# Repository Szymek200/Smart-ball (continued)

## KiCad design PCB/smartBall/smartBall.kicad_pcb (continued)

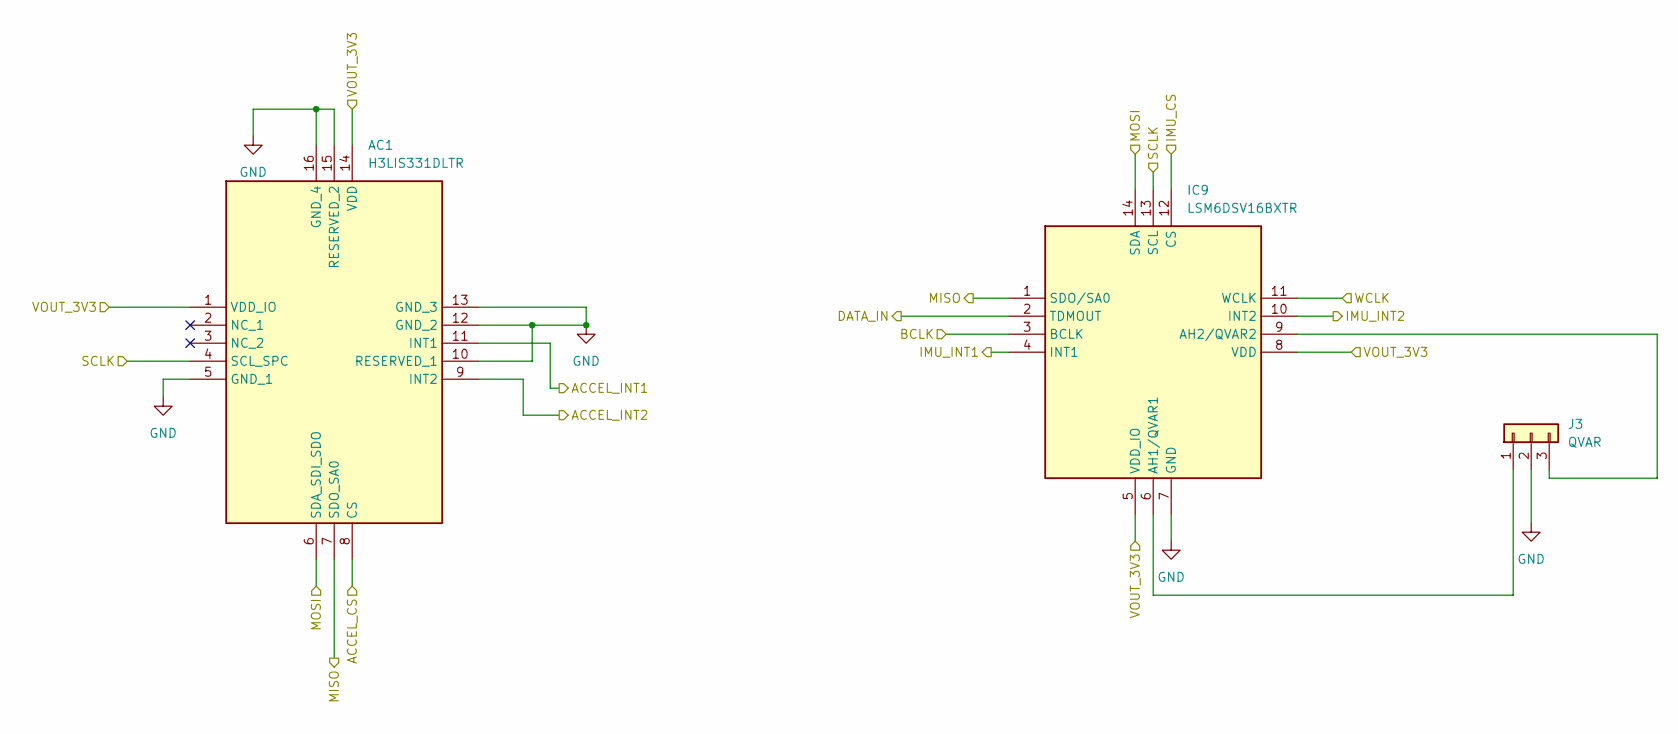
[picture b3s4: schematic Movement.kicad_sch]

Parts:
AC1: H3LIS331DLTR; LIS3DHTR; Mouser Part Number 511-H3LIS331DLTR
IC9: LSM6DSV16BXTR; Mouser Part Number 511-LSM6DSV16BXTR
J3: QVAR; JST_PH_B3B-PH-K_1x03_P2.00mm_Vertical

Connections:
/Power/Movement/ACCEL_CS: AC1.8 (CS); also elsewhere on the board
/Power/Movement/ACCEL_INT1: AC1.11 (INT1); also elsewhere on the board
/Power/Movement/ACCEL_INT2: AC1.9 (INT2); also elsewhere on the board
/Power/Movement/BCLK: IC9.3 (BCLK); also elsewhere on the board
/Power/Movement/DATA_IN: IC9.2 (TDMOUT); also elsewhere on the board
/Power/Movement/IMU_CS: IC9.12 (CS); also elsewhere on the board
/Power/Movement/IMU_INT1: IC9.4 (INT1); also elsewhere on the board
/Power/Movement/IMU_INT2: IC9.10 (INT2); also elsewhere on the board
/Power/Movement/MISO: AC1.7 (SDO_SA0), IC9.1 (SDO/SA0); also elsewhere on the board
/Power/Movement/MOSI: AC1.6 (SDA_SDI_SDO), IC9.14 (SDA); also elsewhere on the board
/Power/Movement/SCLK: AC1.4 (SCL_SPC), IC9.13 (SCL); also elsewhere on the board
/Power/Movement/VOUT_3V3: AC1.1 (VDD_IO), AC1.14 (VDD), IC9.5 (VDD_IO), IC9.8 (VDD); also elsewhere on the board
/Power/Movement/WCLK: IC9.11 (WCLK); also elsewhere on the board
GND: AC1.5 (GND_1), AC1.10 (RESERVED_1), AC1.12 (GND_2), AC1.13 (GND_3), AC1.15 (RESERVED_2), AC1.16 (GND_4), IC9.7 (GND), J3.2; also elsewhere on the board
unnamed: IC9.6 (AH1/QVAR1), J3.1
unnamed: IC9.9 (AH2/QVAR2), J3.3

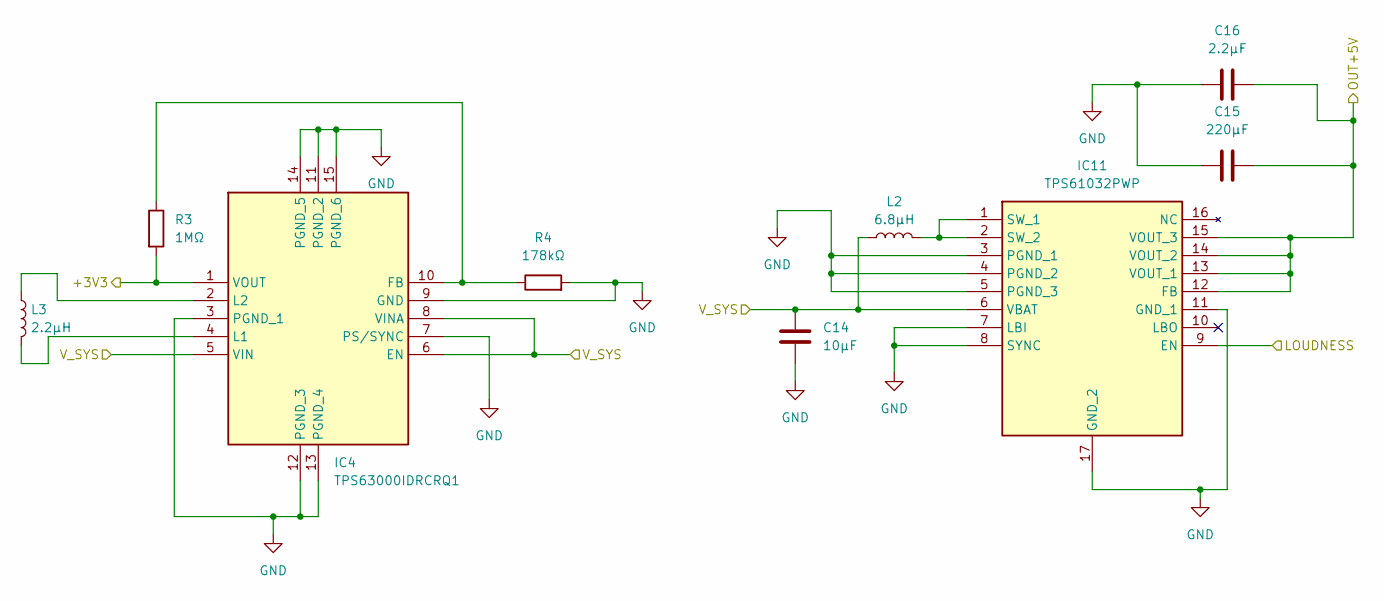
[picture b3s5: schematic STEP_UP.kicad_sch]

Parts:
C14: 10µF; C_Disc_D5.0mm_W2.5mm_P2.50mm
C15: 220µF; C_Disc_D5.0mm_W2.5mm_P2.50mm
C16: 2.2µF; C_Disc_D5.0mm_W2.5mm_P2.50mm
IC4: TPS63000IDRCRQ1; Mouser Part Number 595-TPS63000IDRCRQ1
IC11: TPS61032PWP; SOP65P640X120-17N; Mouser Part Number 595-TPS61032PWP
L2: 6.8µH; L_Axial_L7.0mm_D3.3mm_P10.16mm_Horizontal_Fastron_MICC
L3: 2.2µH; L_Axial_L7.0mm_D3.3mm_P10.16mm_Horizontal_Fastron_MICC
R3: 1MΩ; R_Axial_DIN0207_L6.3mm_D2.5mm_P7.62mm_Horizontal
R4: 178kΩ; R_Axial_DIN0207_L6.3mm_D2.5mm_P7.62mm_Horizontal

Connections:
/Power/Movement/VOUT_3V3: IC4.1 (VOUT), R3.2; also elsewhere on the board
/Power/STEP_UP/LOUDNESS: IC11.9 (EN); also elsewhere on the board
/Power/STEP_UP/OUT+5V: C15.1, C16.2, IC11.12 (FB), IC11.13 (VOUT_1), IC11.14 (VOUT_2), IC11.15 (VOUT_3); also elsewhere on the board
/Power/V_SYS: C14.1, IC4.5 (VIN), IC4.6 (EN), IC4.8 (VINA), IC11.6 (VBAT), L2.1; also elsewhere on the board
GND: C14.2, C15.2, C16.1, IC4.3 (PGND_1), IC4.7 (PS/SYNC), IC4.9 (GND), IC4.11 (PGND_2), IC4.12 (PGND_3), IC4.13 (PGND_4), IC4.14 (PGND_5), IC4.15 (PGND_6), IC11.3 (PGND_1), IC11.4 (PGND_2), IC11.5 (PGND_3), IC11.7 (LBI), IC11.8 (SYNC), IC11.11 (GND_1), IC11.17 (GND_2), R4.2; also elsewhere on the board
unnamed: IC4.10 (FB), R3.1, R4.1
unnamed: IC4.4 (L1), L3.2
unnamed: IC4.2 (L2), L3.1
unnamed: IC11.1 (SW_1), IC11.2 (SW_2), L2.2

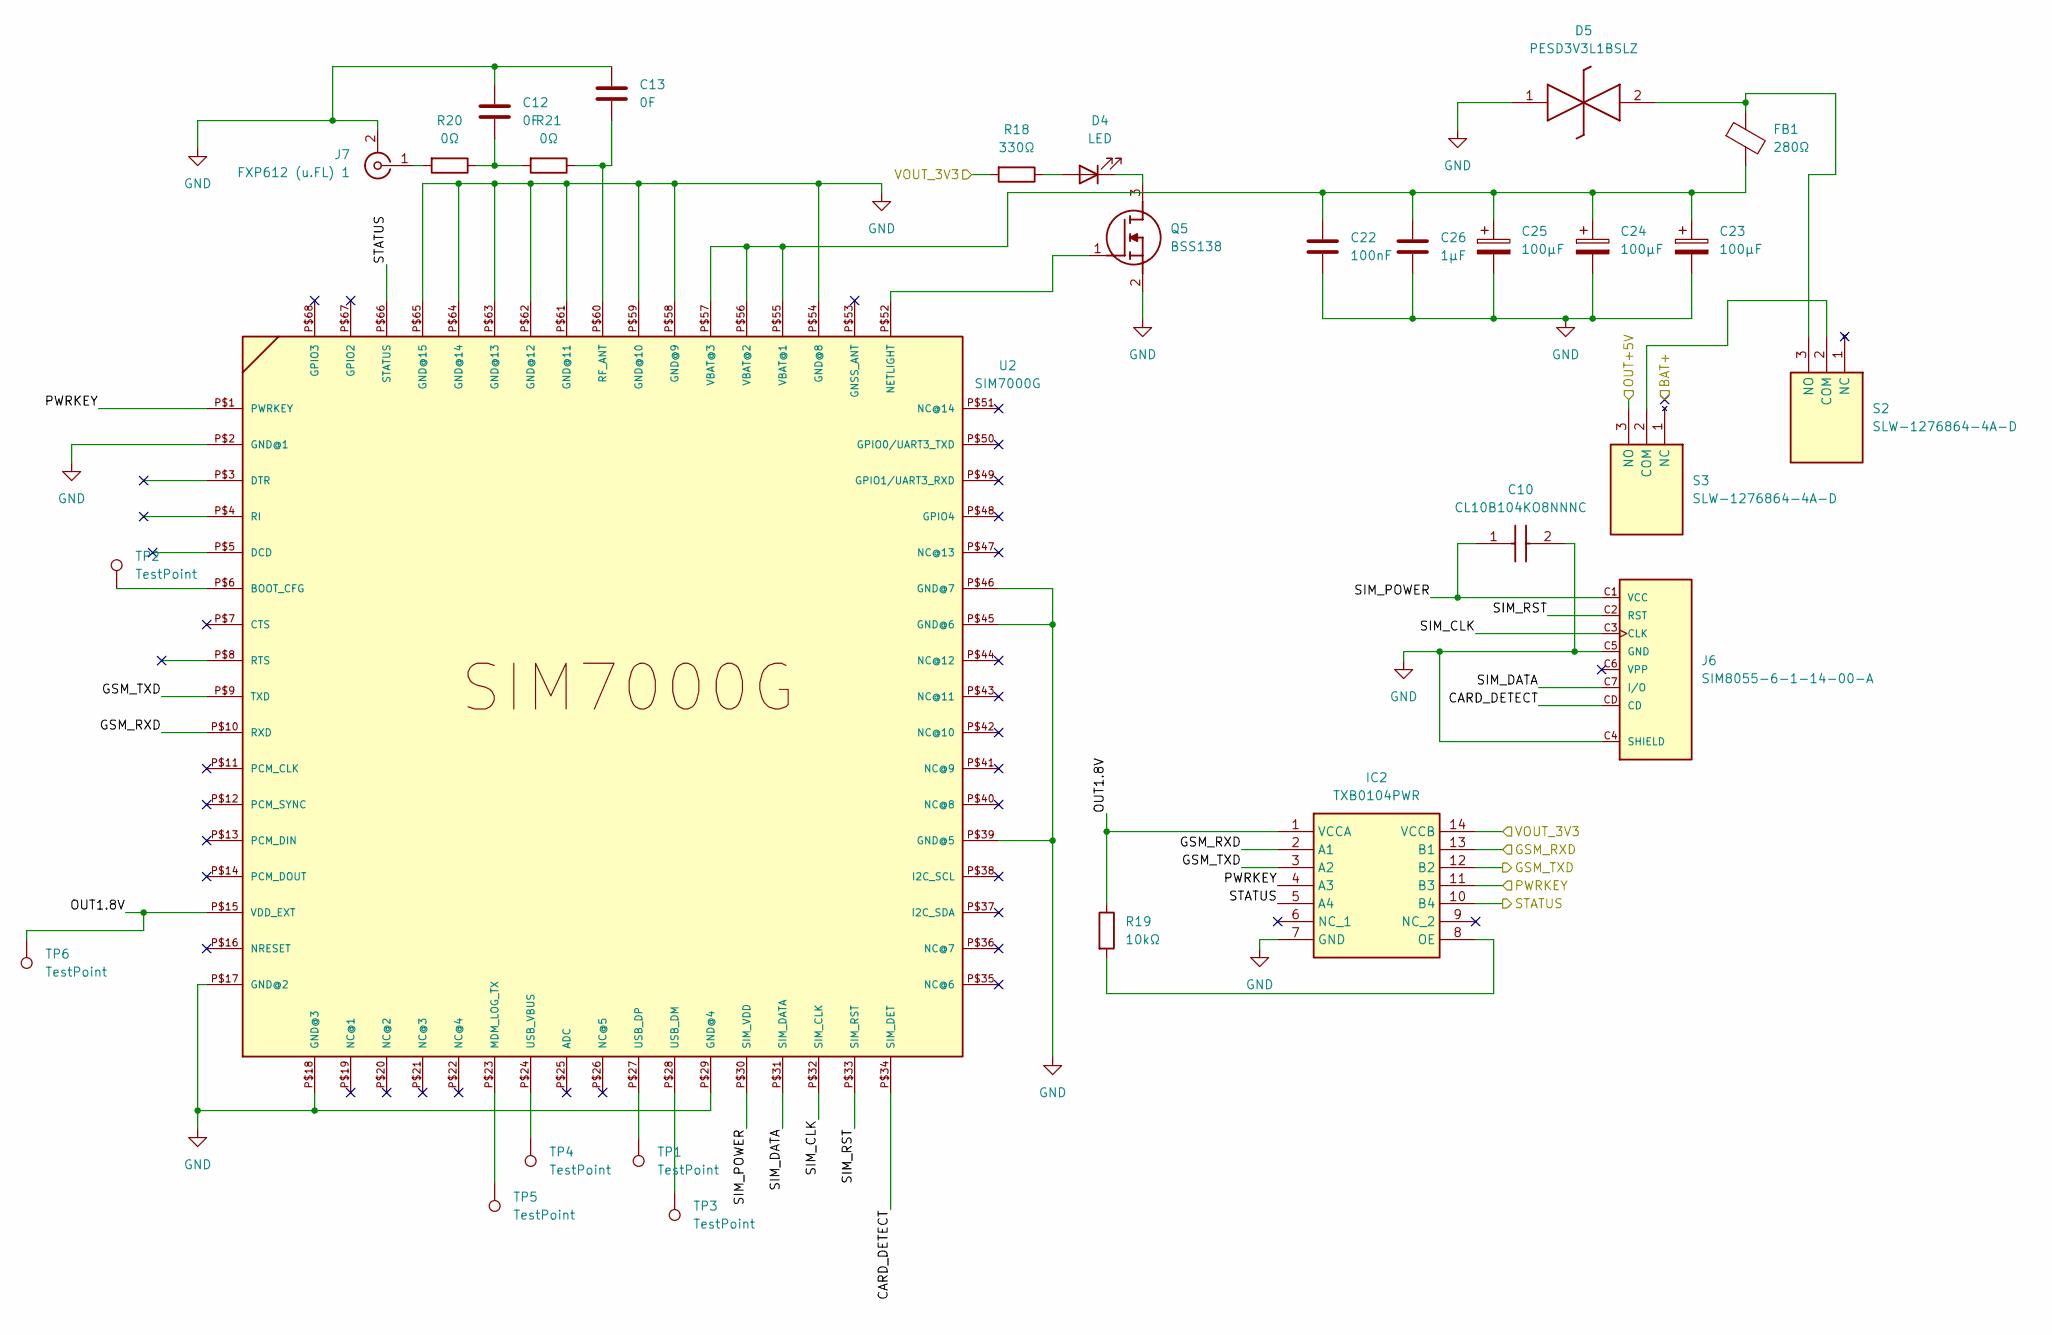
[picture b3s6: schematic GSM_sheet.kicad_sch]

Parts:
C10: CL10B104KO8NNNC; CAPC1608X90N; Mouser Part Number 187-CL10B104KO8NNNC
C12, C13: 0F; C_Disc_D5.0mm_W2.5mm_P2.50mm
C22: 100nF; CP_Radial_Tantal_D5.0mm_P2.50mm
C23, C24, C25: 100µF; CP_Radial_Tantal_D5.0mm_P2.50mm
C26: 1µF; C_Disc_D5.0mm_W2.5mm_P2.50mm
D4: LED; D_DO-41_SOD81_P7.62mm_Horizontal
D5: PESD3V3L1BSLZ; Mouser Part Number 771-PESD3V3L1BSLZ
FB1: 280Ω; L_0805_2012Metric_Pad1.05x1.20mm_HandSolder
IC2: TXB0104PWR; SOP65P640X120-14N; Mouser Part Number 595-TXB0104PWR
J6: SIM8055-6-1-14-00-A; GCT_SIM8055-6-1-14-00-A; PARTREV A1
J7: FXP612 (u.FL) 1; U.FL_Molex_MCRF_73412-0110_Vertical
Q5: BSS138; SOT95P240X120-3N; Mouser Part Number 512-BSS138
R18: 330Ω; R_Axial_DIN0207_L6.3mm_D2.5mm_P7.62mm_Horizontal
R19: 10kΩ; R_Axial_DIN0207_L6.3mm_D2.5mm_P7.62mm_Horizontal
R20, R21: 0Ω; R_Axial_DIN0207_L6.3mm_D2.5mm_P7.62mm_Horizontal
S2, S3: SLW-1276864-4A-D; SLW12768644AD; Mouser Part Number 179-SLW-1276864-4A-D
TP1, TP2, TP3, TP4, TP5, TP6: TestPoint; TestPoint_THTPad_D2.0mm_Drill1.0mm
U2: SIM7000G

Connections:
/+3V3: IC2.14 (VCCB), R18.2; also elsewhere on the board
/OUT+5V: S3.3 (NO); also elsewhere on the board
/PWRKEY: IC2.4 (A3), IC2.11 (B3), U2.P$1 (PWRKEY); also elsewhere on the board
/STATUS: IC2.5 (A4), IC2.10 (B4), U2.P$66 (STATUS); also elsewhere on the board
/Stationary/GSM_sheet/CARD_DETECT: J6.CD, U2.P$34 (SIM_DET)
/Stationary/GSM_sheet/OUT1.8V: IC2.1 (VCCA), R19.1, TP6.1 (1_1), U2.P$15 (VDD_EXT)
/Stationary/GSM_sheet/SIM_CLK: J6.C3 (CLK), U2.P$32 (SIM_CLK)
/Stationary/GSM_sheet/SIM_DATA: J6.C7 (I/O), U2.P$31 (SIM_DATA)
/Stationary/GSM_sheet/SIM_POWER: C10.1, J6.C1 (VCC), U2.P$30 (SIM_VDD)
/Stationary/GSM_sheet/SIM_RST: J6.C2 (RST), U2.P$33 (SIM_RST)
GND: C10.2, C12.1, C13.1, C22.2, C23.2, C24.2, C25.2, C26.2, D5.1 (K1), IC2.7 (GND), J6.C4 (SHIELD), J6.C5 (GND), J6.C8 (SHIELD), J7.2 (Ext), Q5.2 (S), U2.P$2 (GND@1), U2.P$17 (GND@2), U2.P$18 (GND@3), U2.P$29 (GND@4), U2.P$39 (GND@5), U2.P$45 (GND@6), U2.P$46 (GND@7), U2.P$54 (GND@8), U2.P$58 (GND@9), U2.P$59 (GND@10), U2.P$61 (GND@11), U2.P$62 (GND@12), U2.P$63 (GND@13), U2.P$64 (GND@14), U2.P$65 (GND@15); also elsewhere on the board
unnamed: C12.2, R20.1, R21.2
unnamed: D4.2 (A), R18.1
unnamed: D4.1 (K), Q5.3 (D)
unnamed: D5.2 (K2), FB1.1, S2.3 (NO)
unnamed: IC2.8 (OE), R19.2
unnamed: J7.1 (In), R20.2
unnamed: Q5.1 (G), U2.P$52 (NETLIGHT)
unnamed: S2.2 (COM), S3.2 (COM)
unnamed: TP2.1 (1_1), U2.P$6 (BOOT_CFG)
unnamed: TP5.1 (1_1), U2.P$23 (MDM_LOG_TX)
unnamed: C13.2, R21.1, U2.P$60 (RF_ANT)
unnamed: TP3.1 (1_1), U2.P$28 (USB_DM)
unnamed: TP1.1 (1_1), U2.P$27 (USB_DP)
unnamed: TP4.1 (1_1), U2.P$24 (USB_VBUS)
unnamed: C22.1, C23.1, C24.1, C25.1, C26.1, FB1.2, U2.P$55 (VBAT@1), U2.P$56 (VBAT@2), U2.P$57 (VBAT@3)

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
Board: 2 copper layers, 103 parts (0 on the bottom side), 126 nets, no tracks yet.

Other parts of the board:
Q2: BSS138; SOT95P240X120-3N

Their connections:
GND: Q2.2 (S); also elsewhere on the board

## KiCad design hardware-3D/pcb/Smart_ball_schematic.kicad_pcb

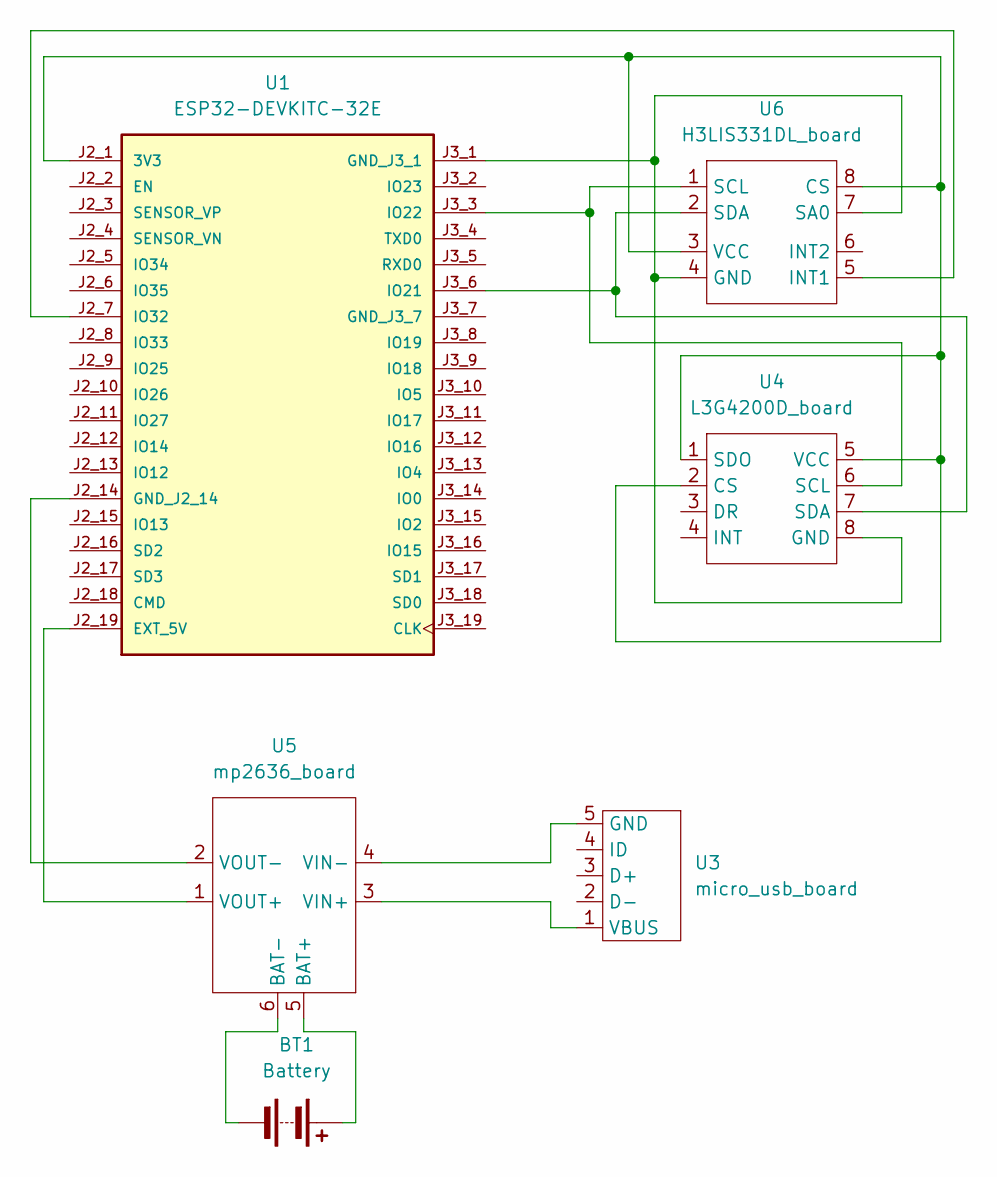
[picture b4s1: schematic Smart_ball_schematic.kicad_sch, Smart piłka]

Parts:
BT1: Battery; battery_foot
U1: ESP32-DEVKITC-32E; MODULE_ESP32-DEVKITC-32E; PARTREV 1.4; DigiKey_Part_Number 1965-ESP32-DEVKITC-32E-ND
U3: micro_usb_board; USB
U4: L3G4200D_board; L3G4200D_foot
U5: mp2636_board; MP2636_foot
U6: H3LIS331DL_board; H3LIS331DL

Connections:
unnamed: BT1.1 (+), U5.5 (BAT+)
unnamed: BT1.2 (-), U5.6 (BAT-)
unnamed: U1.J2_1 (3V3), U4.1 (SDO), U4.2 (CS), U4.5 (VCC), U6.3 (VCC), U6.8 (CS)
unnamed: U1.J2_19 (EXT_5V), U5.1 (VOUT+)
unnamed: U1.J2_14 (GND_J2_14), U5.2 (VOUT-)
unnamed: U1.J3_1 (GND_J3_1), U4.8 (GND), U6.4 (GND), U6.7 (SA0)
unnamed: U1.J3_6 (IO21), U4.7 (SDA), U6.2 (SDA)
unnamed: U1.J3_3 (IO22), U4.6 (SCL), U6.1 (SCL)
unnamed: U1.J2_7 (IO32), U6.5 (INT1)
unnamed: U3.5 (GND), U5.4 (VIN-)
unnamed: U3.1 (VBUS), U5.3 (VIN+)

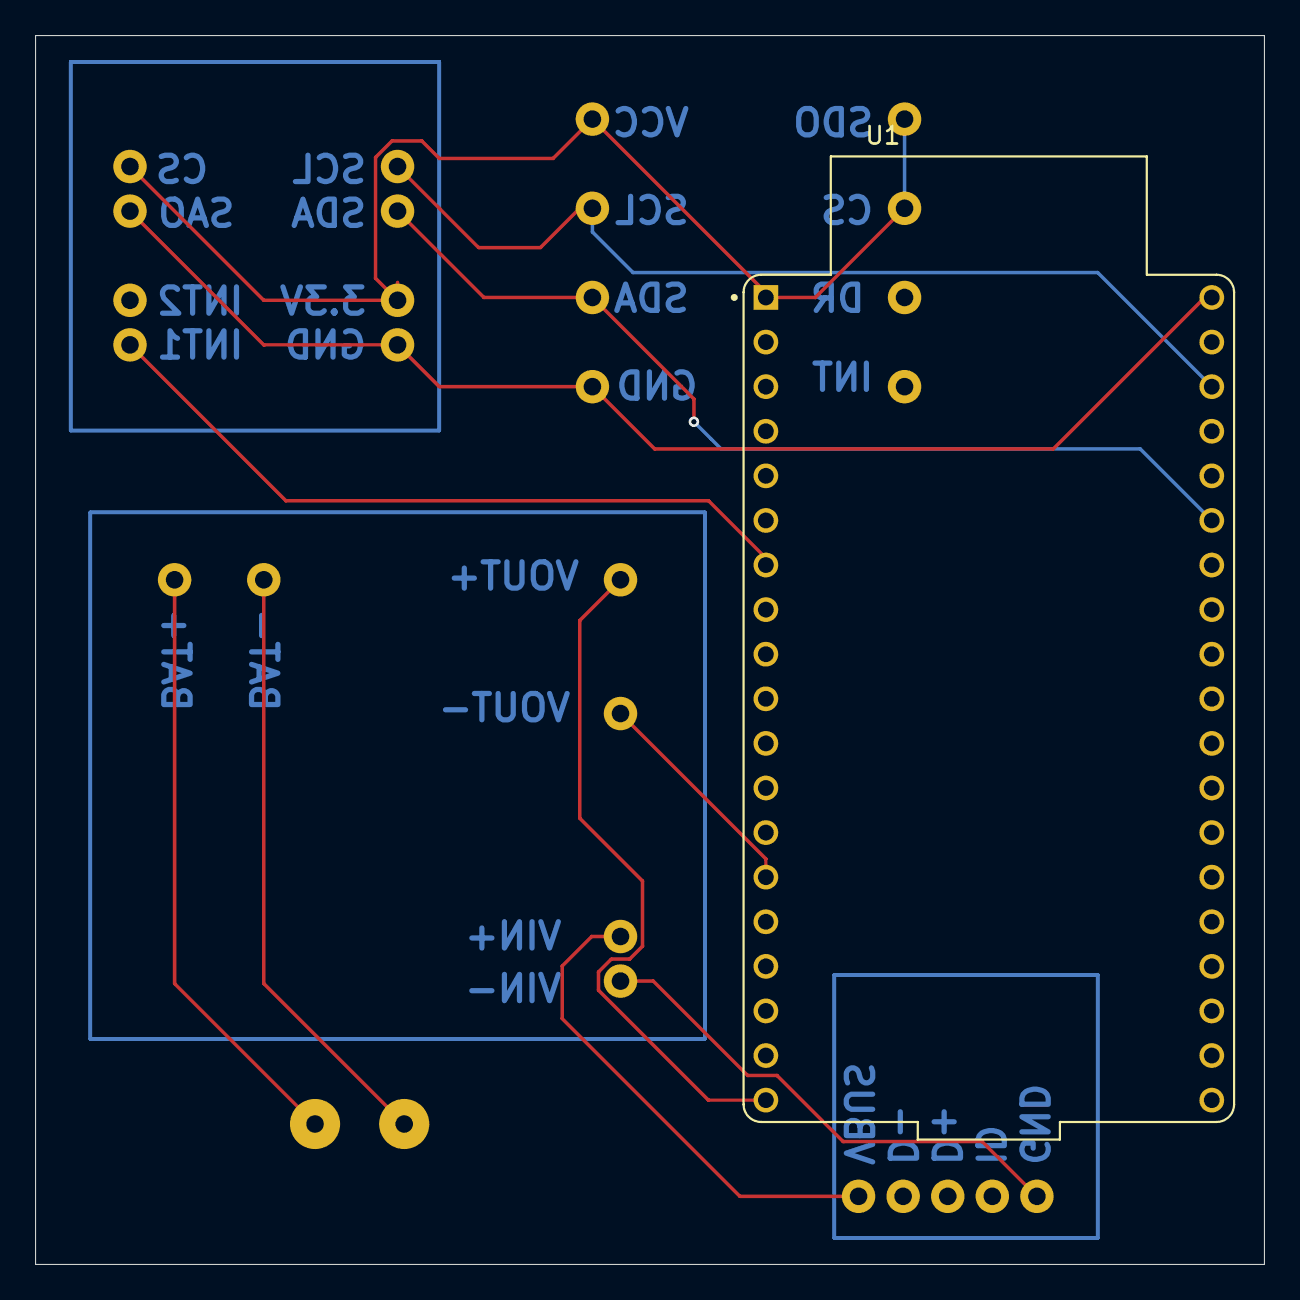
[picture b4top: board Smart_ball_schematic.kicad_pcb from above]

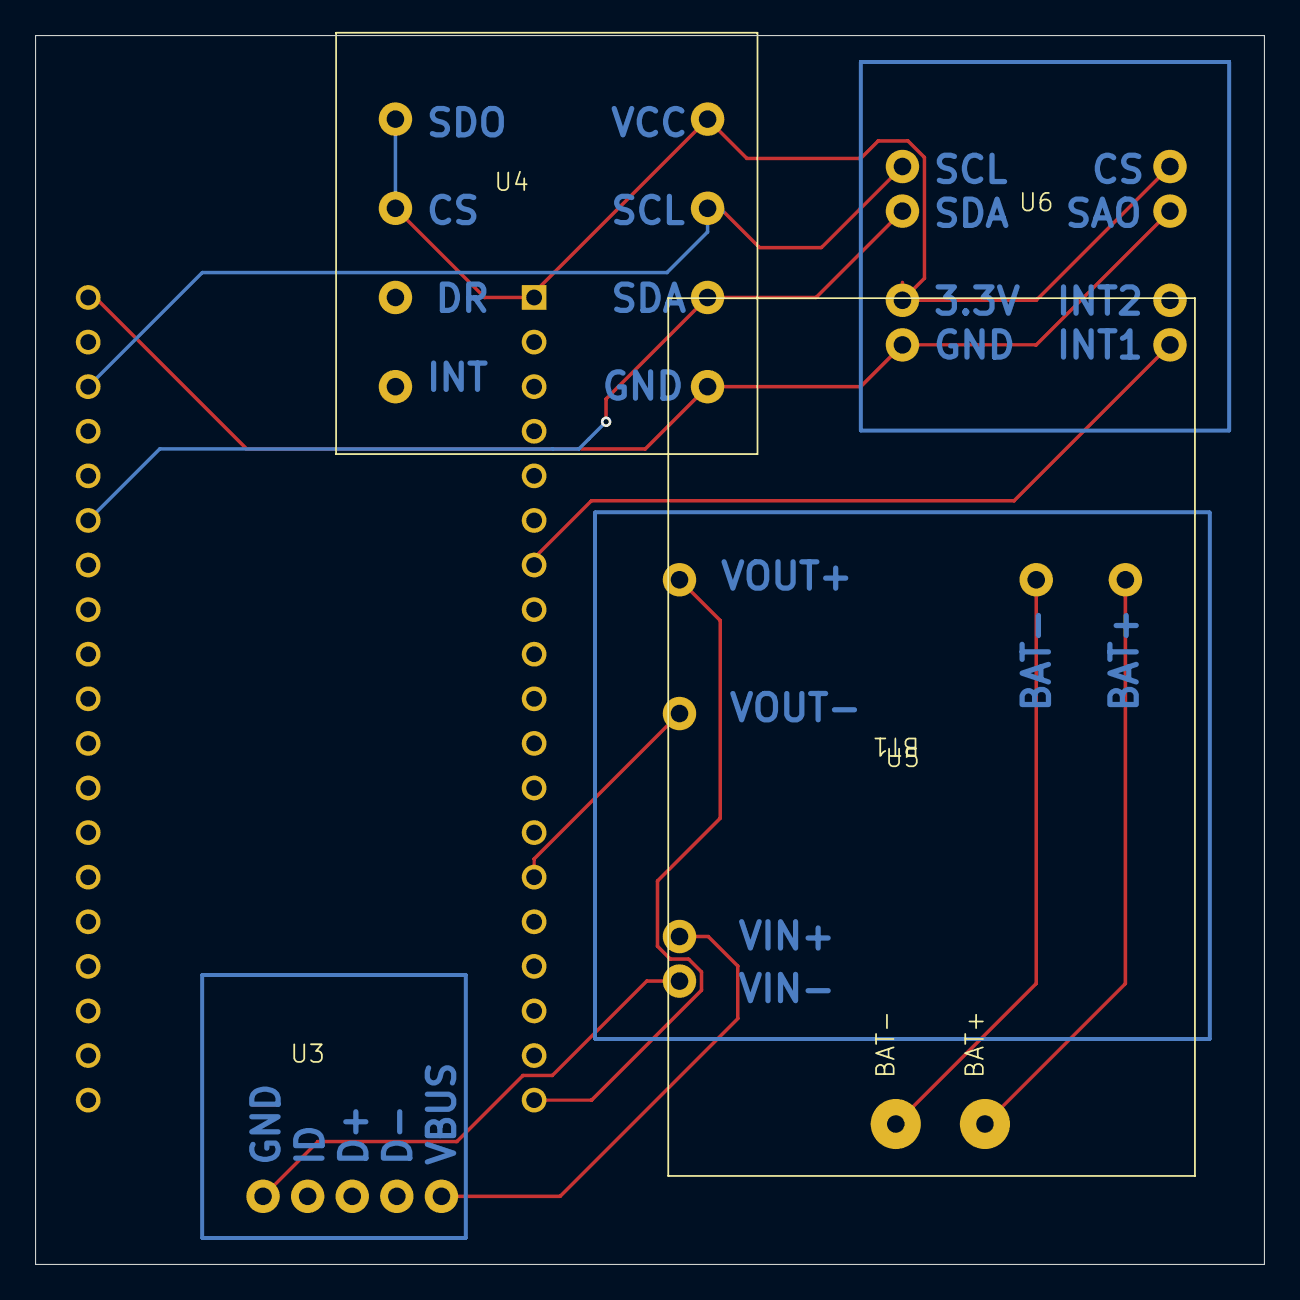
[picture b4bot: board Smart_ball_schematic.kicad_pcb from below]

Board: 2 copper layers, 70.0 x 70.0 mm, 6 parts (5 on the bottom side), 11 nets.

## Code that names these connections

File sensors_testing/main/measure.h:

#ifndef MEASURE_H
#define MEASURE_H

#include <stdint.h>           
#include <stdbool.h> 
#include <math.h> 

#include "freertos/FreeRTOS.h"
#include "freertos/queue.h"
#include "driver/spi_master.h"
#include "esp_event.h"        

// Kolejki FreeRTOS
extern QueueHandle_t data_queue;
extern QueueHandle_t gps_queue;

// Zmienne konfiguracyjne z NVS / systemowe
extern float config_wake_ths_g;
extern float config_sleep_ths_g;
extern int config_idle_time_s;
extern float crash_threshold_g; 
extern int config_sensor_loop_ms;
extern bool config_enable_sleep; 

// Flagi stanu peryferiów
extern bool is_gps_connected; 
extern bool is_phone_connected;

// Piny magistrali SPI
#define PIN_MISO            17
#define PIN_MOSI            18
#define PIN_SCLK            8

// Akcelerometr H3LIS331DL
#define PIN_ACCEL_CS        14
#define PIN_ACCEL_INT1      21  // Pin wybudzania ESP32 z trybu Light Sleep

// IMU LSM6DSV16X
#define PIN_IMU_CS          13  

// GPS UART
#define GPS_RX_PIN          5   // TX z modułu GPS -> RX w ESP32
#define GPS_TX_PIN          15  // RX w module GPS <- TX z ESP32

// Parametry buforowania zderzenia
#define PRE_HIT_BUFFER_SIZE  100
#define POST_HIT_SAMPLES     100

// Struktury danych
typedef struct {
    float x;
    float y;
    float z;
} vector3d_t; 

typedef struct {
    uint8_t packet_type; // 0: Lot/Normalny, 1: Zderzenie (Hit)
    vector3d_t accel_h3lis;
    vector3d_t accel_imu;
    vector3d_t gyro;
    float latitude;
    float longitude;
    bool gps_fix;
    float battery_voltage;
    float battery_percent;
} __attribute__((packed)) global_data_t;

typedef struct {
    spi_device_handle_t spi_handle; 
    uint8_t cs_pin; 
} sensor_spi_handle_t;

typedef struct {
    struct { float x; float y; float z; } accel; 
    struct { float x; float y; float z; } gyro;  
    struct { float x; float y; float z; float w; } quat; 
} imu_data;

// Funkcje inicjalizacyjne i kontrolne
void sensors_set(bool GPS_on);
void accel_set(void);
void imu_set(void);
void sensors_task_start(void);
void sensors_enter_light_sleep(void);

// Odczyt danych z sensorów
vector3d_t accel_get(void);
imu_data imu_get(void);
global_data_t convert_to_global_frame(void);

// Obsługa GPS
void gps_start(void);
bool get_gps_hardware_status(void);
void get_last_gps_data(float *lat, float *lon, bool *fix);

// Diagnostyka
void log_global_data(const global_data_t *data);

#endif // MEASURE_H

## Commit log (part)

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2025-10-02 Create beginning
    Dowloading repo to PC
2025-10-04 Prezentacja zarys
2025-10-04 Datasheets dodanie
2025-10-07 skonczona prezentacja
2025-10-28 prez dod srodowisko
2025-10-28 prezentacja gotowa
2025-10-29 stm32
2025-10-31 dane w karcie projektu
2025-10-31 karta projektu v2
2025-11-12 pomiary z czujnikow
2025-11-22 przetwarzanie dziala
2025-11-25 nie uruchamia sie
2026-02-12 esp project added
2026-02-12 android app
2026-02-28 organizing files
2026-02-28 organising docs
2026-03-06 added readme files
2026-03-22 datasheet for all components
2026-04-05 first shot schematic diagram
2026-04-05 cleaning repository
2026-04-05 updated git ignore
2026-04-08 schematic ready
2026-04-08 footprints assigned
2026-04-09 pcb start
2026-04-14 updated to hierarchical labels
2026-04-15 new footprints assigned
2026-04-15 last modifications schematic
2026-04-15 grouping things on pcb
2026-04-15 everything on pcb
2026-04-15 routing done
2026-04-15 chips on pcb
2026-04-15 routing and holes added
2026-04-16 programming MCU pins
2026-04-16 everything before jlc template
2026-04-18 working on routing
2026-04-19 verifying schematic and 3V8 power for gsm
2026-04-19 induction verified
2026-04-20 ECR passed
2026-04-21 routing on your own
2026-04-21 two layers routing done
2026-04-22 own routes with errors done
2026-04-23 most errors solved
2026-04-23 DRC passed
2026-04-23 boards done
2026-04-24 everything checked
2026-04-24 everything done before changing footprints
2026-04-28 before deleting C10
2026-04-28 all my pcb
2026-04-30 imu from board
2026-04-30 accel changed to goldpin
2026-04-30 ATA connector updated
2026-05-01 before smd
2026-05-02 goldpins on one side
2026-05-03 modified gnd
2026-05-03 bought pcbs
2026-05-03 invoice added
2026-05-06 more invoices
2026-05-24 restoring data for soldering
2026-06-03 accel and imu in two tasks
2026-06-04 gps compiles
2026-06-07 modified to TCP connection
2026-06-08 generall code for all sensors
